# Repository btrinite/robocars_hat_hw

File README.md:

# This repository contains the hardware part of the DIYRobocarsFr Hat.

## Intro
This Hat is designed for Raspberry Pi 3/4, Jetson Nano or any other SBC implementing the well known 'rpi' GPIO connector.
This Hat provides various interfaces between SBC (Single Board Controler) and hardware to easely build an autonomous small scale RC-style car.
A typical example of such build is the [Donkey car](https://www.donkeycar.com/)

The Hat combines :
- LM2596 or xl4005 DSN5000 based DC/DC converter to power everything from a single battery (7-15V, NiMh or LiPo 2S/3S), through GPIO or through dedicated connector.
- Arduino pro mini 5V 16Mhz, which drive I/O (PWM Inpput/output, Ultrasonic sensor, RPM sensor, ...). 5V version is prefered since most of the sensors works at 5v.
- Serial communication link between Arduino and SBC through GPIO pin 8 and 10, with level shift 5v/3.3V 
- Tension divider bridge for Battery monitoring
- RBG Led to display status
- compatibility (stackable) with Arducam CamArray

The Hat has the following I/O :
- 40 pin header GPIO compatible with Raspberry PI and Nvidia Jetson with UART0 wired to the arduino through level shift
- 3 Battery power in connectors (2 wires, 3 wires or 4 wires)
- 2 PWM Inputss to connect RC Receiver (Throttle and Steering input)
- 2 PWM Outputs to connect drive train (ESC and Servo, for Throttle and Steering output) 
- 2 PWM Aux Inputs/Outputs
- 1 input for RPM sensor
- 1 input for UltraSOund sensor
- Aux connector for additional power output (5V and 3.3V) and to stack ArduCam CamArray
- WS2812B compatible output to control more RGB Led

The follwing jumpers are provided for convenience :
- 5V to GPIO : to inject 5V power supply to the Host through GPIO connector (to power Raspberry or Jetson Nano from the main Battery).
For other Hosts, please check documentation
- UART0 RX/TX Jumper : Usually, you need those jumpers since all communication between Host and Hat goes through this UART. Removing those jumpers could be needed to isolate Arduino UART while re-flashing it (especially if Host is powered on at flahsing time).

## Wiring
A typical wiring of the Hat is shown below : 

## Schematic

Consult [Schematics.pdf](doc/Schematics.pdf)

## Note on PWM Block

### Power supply
Hat does not provide power supply through PWM Inputs/Outpus. It is usualy duty of the motor controller (ESC) which feature a BEC.
This is to avoid mixing logic and actuators on the same power source. It means that as long as ESC is not connected and switchded on, Servo and RX Receiver will not be powered.

### output Idle signal
In the current implementation,

- First, as soon as the Hat is powered, a default Idle signal is driven (1,5ms pulse width)
This default idle signal could differ from the one you could have when doing calibration. 

- Second, many ESC will autocalibrate to this idle signal at startup time (when switched on) 

If you are in that case, it is recommanded to switch on the ESC only after the main application is up and running.

## Dependencies

Third party components libraries needed :

* [LM2596 DC to DC buck/step-down module](https://github.com/yet-another-average-joe/KiCad-Chinese_Modules/tree/main/DCDC_StepDown_LM2596)

* https://github.com/g200kg/kicad-lib-arduino.git

## Firmware

### Source
Firmware to upload to the Arduino ca be found [here](https://github.com/btrinite/robocars_hat)

### Flash firmware
To flash firmware, you need to connect a 5V FTDI adaptor featuring DTR signal and use Arduino IDE to flash/upload the content.
Do not forget to solder Pin header connector on Arduino Pins dedicated for uploading/flash purpose.
You can find more informations [here](https://www.arduino.cc/en/Guide/ArduinoProMini)

## Troubleshooting

### Loopback test (only applicable when using SimpleSerial protocol version of the firmware)
SimpleSerial protocol messages that carry throttle and steering are almost symetrical. Thus, if you loopback the serial comunication (RX wired to TX), the Hat will
work in loopback mode. Throttle/Steering orders received from RX Receiver will be used to drive Throttle/Steering output.

Loopback mode is achieved by :
- removing Rx/Tx jumpers to decouple UART signal from Host
- Wiring Rx and Tx together

This is illsutrated below : 

## Example of integration
Modified Donkeycar software with integration of the DIYRobocarsFr Hat is available [here](https://github.com/btrinite/donkey_with_robocars_hat)

## Credits
Based on https://github.com/devbisme/RPi_Hat_Template

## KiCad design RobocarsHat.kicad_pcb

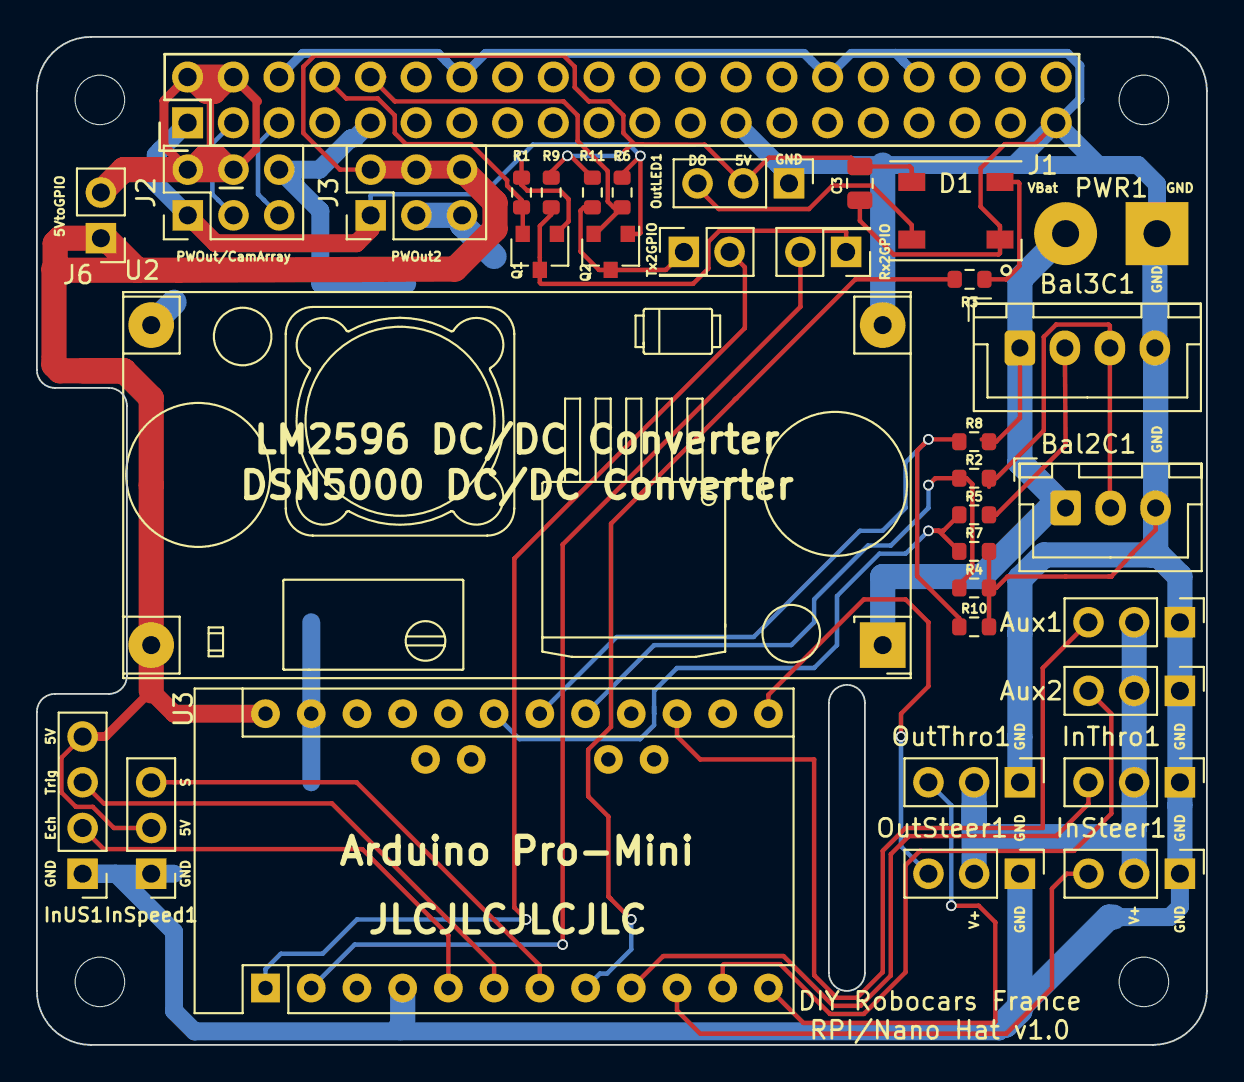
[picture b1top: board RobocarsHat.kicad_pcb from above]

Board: 2 copper layers, 65.0 x 56.0 mm, 35 parts (0 on the bottom side), 31 nets.

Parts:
Aux1, Aux2: Conn_01x03_Male; PinHeader_1x03_P2.54mm_Vertical
Bal2C1: PWR2; JST_XH_B3B-XH-A_1x03_P2.50mm_Vertical
Bal3C1: PWR3; JST_XH_B4B-XH-A_1x04_P2.50mm_Vertical
C3: 100nF; C_0805_2012Metric
D1: WS2812B; LED_WS2812B_PLCC4_5.0x5.0mm_P3.2mm
InSpeed1: Conn_01x03_Male; PinHeader_1x03_P2.54mm_Vertical
InSteer1: Conn_01x03_Male; PinHeader_1x03_P2.54mm_Vertical
InThro1: Conn_01x03_Male; PinHeader_1x03_P2.54mm_Vertical
InUS1: Conn_01x04_Male; PinHeader_1x04_P2.54mm_Vertical
J1: RPi_GPIO; Pin_Header_Straight_2x20
J2: PWOut/Camarray; Pin_Header_Straight_2x03_Pitch2.54mm
J3: PWOut; Pin_Header_Straight_2x03_Pitch2.54mm
J4, J5: Conn_01x02_Male; PinHeader_2x01_P2.54mm_Vertical
J6: Conn_01x02_Male; PinHeader_1x02_P2.54mm_Vertical
OutLED1: Conn_01x03_Male; PinHeader_1x03_P2.54mm_Vertical
OutSteer1: Conn_01x03_Male; PinHeader_1x03_P2.54mm_Vertical
OutThro1: Conn_01x03_Male; PinHeader_1x03_P2.54mm_Vertical
PWR1: PWR1; SolderWirePad_1x02_P5.08mm_Drill1.5mm
Q1, Q2: BSS138; SOT-23
R1, R6, R9, R11: 10K; R_0603_1608Metric
R2, R5, R8: 100k; R_0603_1608Metric
R3: 150R; R_0603_1608Metric
R4, R7, R10: 10k; R_0603_1608Metric
U2: LM2596; YAAJ_DCDC_StepDown_LM2596
U3: Arduino_Pro_Mini

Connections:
+3V3: J1.1, J2.1, J3.1, Q1.1, Q2.1, R1.1, R6.1
GND: Aux1.1, Aux2.1, Bal2C1.3, Bal3C1.4, C3.2, D1.3, InSpeed1.1, InSteer1.1, InThro1.1, InUS1.1, J1.6, J1.9, J1.14, J1.25, J1.30, J1.34, J1.39, J2.6, J3.3, J3.5, OutLED1.1, OutSteer1.1, OutThro1.1, PWR1.1, R4.2, R7.2, R10.2, U2.2, U2.3, U3.4, U3.23
unnamed: Aux1.2, Aux2.2, InSteer1.2, InThro1.2, OutSteer1.2, OutThro1.2
unnamed: Aux1.3, U3.15
unnamed: Aux2.3, U3.11
unnamed: Bal2C1.1, Bal3C1.1, PWR1.2, R8.1, U2.1
unnamed: Bal2C1.2, Bal3C1.3, R2.1
unnamed: Bal3C1.2, R5.1
unnamed: D1.2, OutLED1.3
unnamed: D1.4, R3.1
unnamed: InSpeed1.3, U3.7
unnamed: InSteer1.3, U3.10
unnamed: InThro1.3, U3.9
unnamed: InUS1.2, U3.5
unnamed: InUS1.3, U3.6
unnamed: J1.2, J1.4, J2.2, J2.4, J6.2
unnamed: J1.3, J2.3
unnamed: J1.5, J2.5
unnamed: J1.8, Q1.2, R1.2
unnamed: J1.10, Q2.2, R6.2
unnamed: J4.1, Q2.3, R11.2
unnamed: J4.2, U3.1
unnamed: J5.1, Q1.3, R9.2
unnamed: J5.2, U3.2
unnamed: OutSteer1.3, U3.13
unnamed: OutThro1.3, U3.12
unnamed: R2.2, R4.1, U3.17
unnamed: R3.2, U3.8
unnamed: R5.2, R7.1, U3.19
unnamed: R8.2, R10.1, U3.18
VCC: C3.1, D1.1, InSpeed1.2, InUS1.4, J3.2, J3.4, J3.6, J6.1, OutLED1.2, R9.1, R11.1, U2.4, U3.24

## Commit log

2021-10-07 update doc
2021-10-11 update dep
2021-10-21 readme + bom
2021-10-27 Wiring
2021-10-28 note on PWM
2021-10-28 md fix
2021-11-29 Loopback mode
